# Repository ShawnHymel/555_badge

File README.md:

555 Badge
=========
Badge project based on a 555 timer circuit. Users can follow along with the Digi-Key video series to design and fabricate their own badge PCB. This repository stores all the completed PCB design files. Click [here to watch the video series](https://www.youtube.com/watch?v=vaCVh2SAZY4&index=1&list=PLEBQazB0HUyR24ckSZ5u05TZHV9khgA1O&t=0s).

Repository Contents
-------------------
* **555_Badge_BOM** - Bill of materials necessary for building the badge
* **/Hardware** - KiCad design files and gerbers to create 1 badge
* **/Images** - Various logos and other images used in the PCB design
* **/Production** - PCBs panelized for a production run (9 badges per panel)

License Information
-------------------
The hardware is released under [Creative Commons Attribution 4.0 International (CC BY 4.0)](https://creativecommons.org/licenses/by/4.0/).

Distributed as-is; no warranty is given.

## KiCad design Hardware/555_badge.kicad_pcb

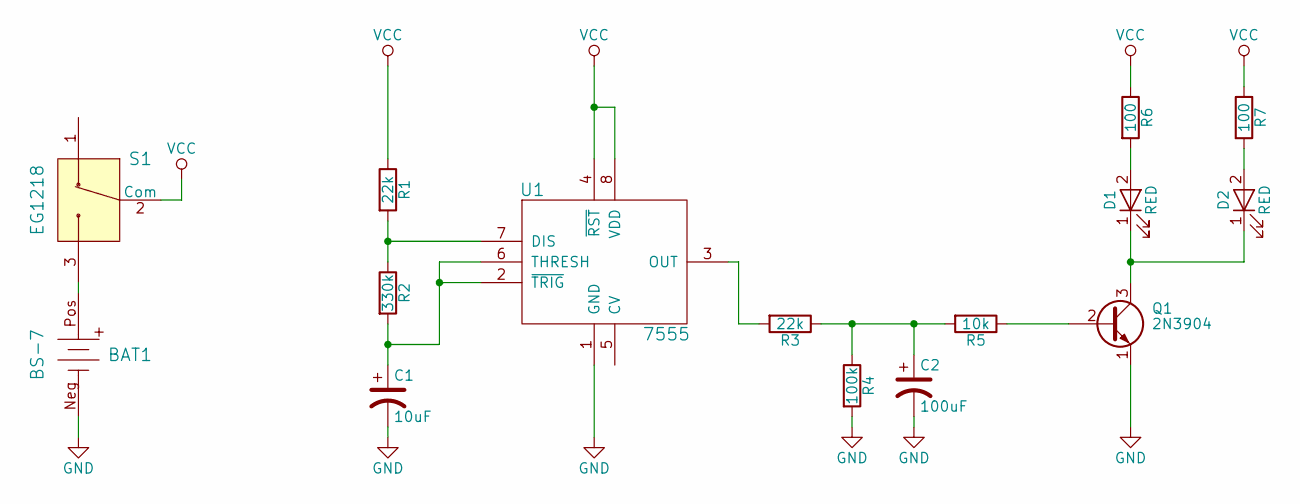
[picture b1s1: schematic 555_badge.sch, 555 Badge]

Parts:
BAT1: BS-7; MPN BS-7; Digi-Key_PN BS-7-ND
C1: 10uF; CP_Radial_D5.0mm_P2.00mm
C2: 100uF; CP_Radial_D6.3mm_P2.50mm
D1, D2: RED; LED_D3.0mm
Q1: 2N3904; TO-92-3
R1, R3: 22k; R_Axial_DIN0207_L6.3mm_D2.5mm_P7.62mm_Horizontal
R2: 330k; R_Axial_DIN0207_L6.3mm_D2.5mm_P7.62mm_Horizontal
R4: 100k; R_Axial_DIN0207_L6.3mm_D2.5mm_P7.62mm_Horizontal
R5: 10k; R_Axial_DIN0207_L6.3mm_D2.5mm_P7.62mm_Horizontal
R6, R7: 100; R_Axial_DIN0207_L6.3mm_D2.5mm_P7.62mm_Horizontal
S1: EG1218; MPN EG1218; Digi-Key_PN EG1903-ND
U1: 7555; ICM7555-PDIP

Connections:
GND: BAT1.Neg, C1.2, C2.2, Q1.1 (E), R4.2, U1.1 (GND)
unnamed: BAT1.Pos, S1.3
unnamed: C1.1, R2.2, U1.2 (~TRIG), U1.6 (THRESH)
unnamed: C2.1, R3.1, R4.1, R5.2
unnamed: D1.1 (K), D2.1 (K), Q1.3 (C)
unnamed: D1.2 (A), R6.2
unnamed: D2.2 (A), R7.2
unnamed: Q1.2 (B), R5.1
unnamed: R1.2, R2.1, U1.7 (DIS)
unnamed: R3.2, U1.3 (OUT)
VCC: R1.1, R6.1, R7.1, S1.2 (Com), U1.4 (~RST), U1.8 (VDD)

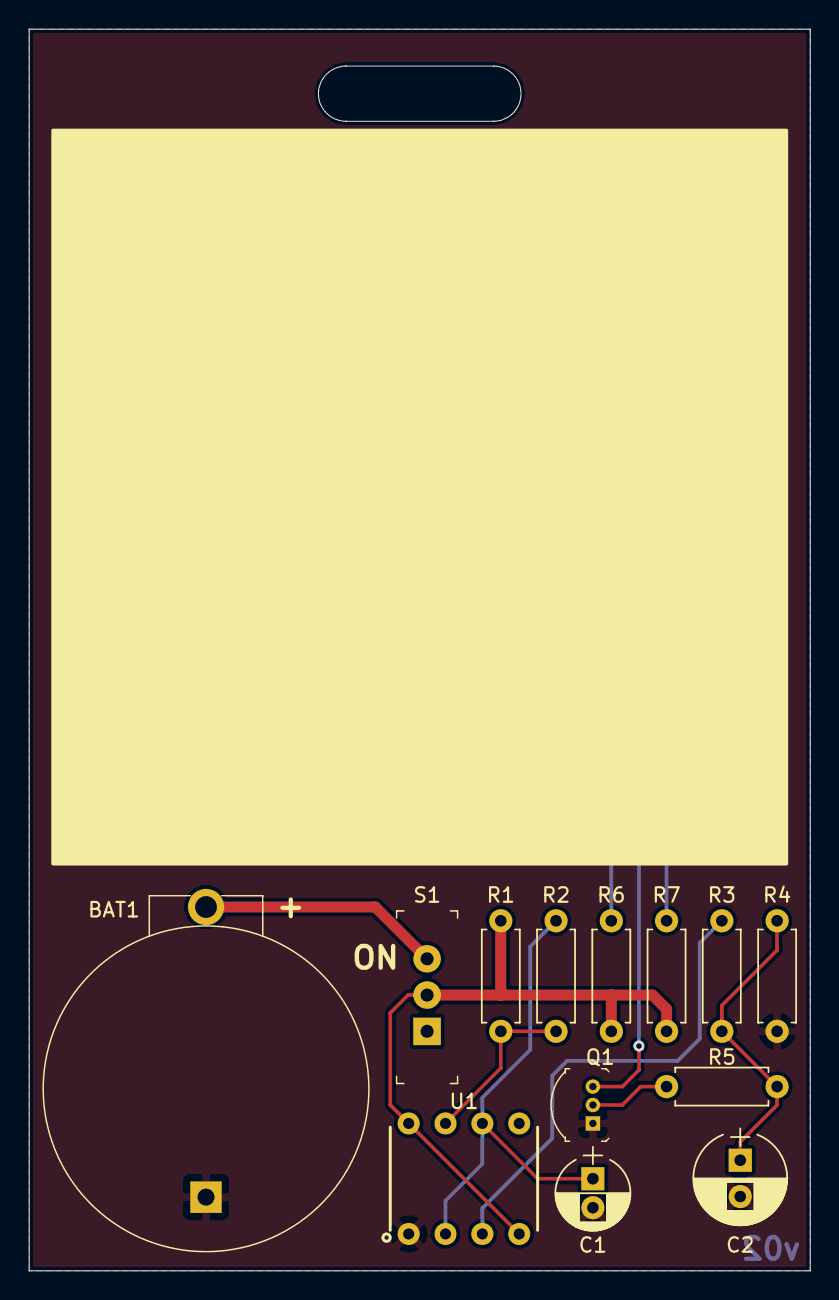
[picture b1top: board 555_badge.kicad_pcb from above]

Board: 2 copper layers, 53.8 x 85.6 mm, 15 parts (0 on the bottom side), 11 nets.

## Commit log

2017-12-27 v00 complete and sent to fab
2018-01-12 v00a. Flipped LEDs, disconnected CV on 7555, widened slot.
2018-01-14 Changed R2 to 330k
2018-04-29 Added some silk. Updated to v02. Panelized design. Created README.
2018-04-30 Added D1 and D2 refdes to back
2018-04-30 Removed lock file
2018-06-28 Flipped transistor silk
2018-08-14 Added a .gitignore to prevent checking in lock files.

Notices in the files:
555_badge.sch:
License: CC BY 4.0
